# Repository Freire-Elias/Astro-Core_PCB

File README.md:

# Astro-Core PCB

Placa de controle baseada em **ESP32**, projetada para a equipe de robótica competitiva OBR **AstroTech**.

---

## What is this project?

This project was designed to create a central module for sensors, control, motors, and monitoring of an OBR robot.
This repository contains all the hardware files (PCB and schematics) for this board.

---

## 3D Board Render

---

## Board Schematic

---

## License

This project is under license **MIT**.  
See [LICENSE](LICENSE) for more details.

---

## 👤 Author

Created by **Elias Freire**  
GitHub: https://github.com/Freire-Elias

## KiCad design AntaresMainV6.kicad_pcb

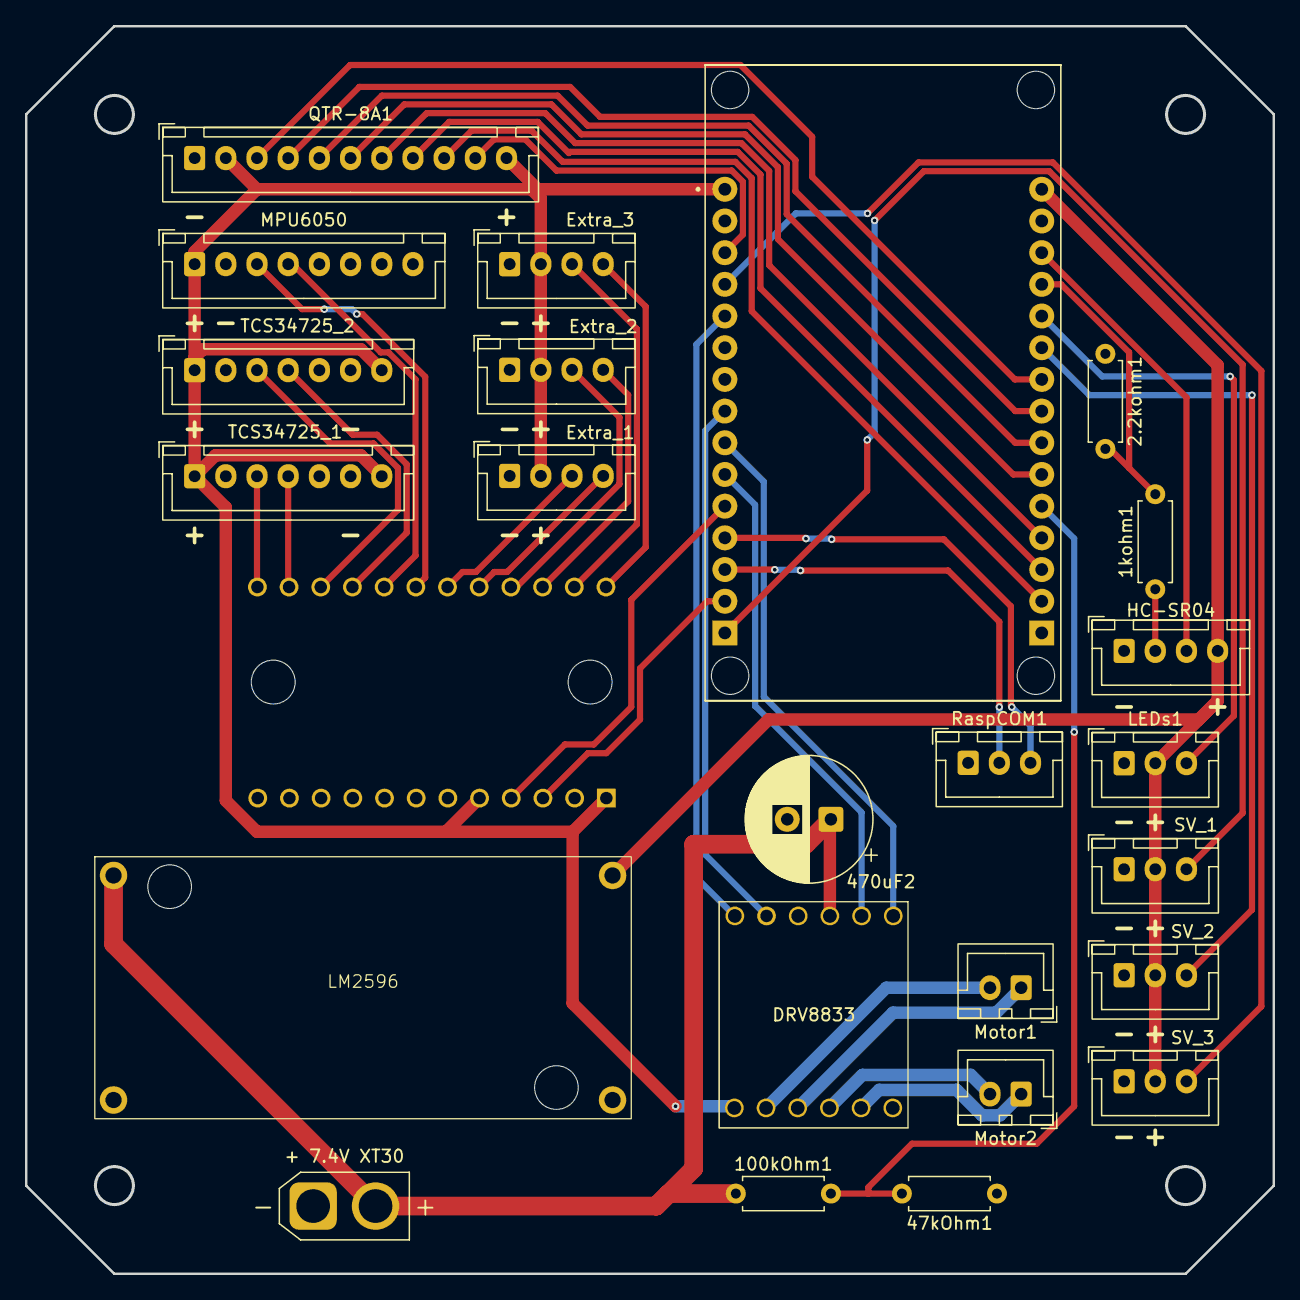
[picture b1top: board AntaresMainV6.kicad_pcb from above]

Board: 2 copper layers, 100.0 x 100.0 mm, 25 parts (1 on the bottom side), 44 nets.

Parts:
1kohm1, 2.2kohm1, 47kOhm1, 100kOhm1: R; R_Axial_DIN0207_L6.3mm_D2.5mm_P7.62mm_Horizontal
470uF2: C_Polarized; CP_Radial_D10.0mm_P3.50mm
+ 7.4V XT30: Conn_01x02_Socket; AMASS_XT30U-M_1x02_P5.0mm_Vertical
DRV8833: DRV8833
Extra_1, Extra_2, Extra_3: Conn_01x04_Socket; JST_XH_B4B-XH-A_1x04_P2.50mm_Vertical
HC-SR04: Conn_01x04_Socket; JST_XH_B4B-XH-A_1x04_P2.50mm_Vertical
LEDs1: Conn_01x03_Socket; JST_XH_B3B-XH-A_1x03_P2.50mm_Vertical
LM2596: Lm2596 DC-DC Buck; Lm2596_ALT
MPU6050: Conn_01x08_Socket; JST_XH_B8B-XH-A_1x08_P2.50mm_Vertical
Motor1, Motor2: Conn_01x02_Socket; JST_XH_B2B-XH-A_1x02_P2.50mm_Vertical
QTR-8A1: Conn_01x11_Socket; JST_XH_B11B-XH-A_1x11_P2.50mm_Vertical
RaspCOM1: Conn_01x03_Socket; JST_XH_B3B-XH-A_1x03_P2.50mm_Vertical
SV_1, SV_2, SV_3: Conn_01x03_Socket; JST_XH_B3B-XH-A_1x03_P2.50mm_Vertical
TCA1: 2717; TCA9548_ALT
TCS34725_1, TCS34725_2: Conn_01x07_Socket; JST_XH_B7B-XH-A_1x07_P2.50mm_Vertical
U3: ESP32-DEVKIT-V1; MODULE_ESP32_DEVKIT_V1

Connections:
/0+: 100kOhm1.1, 470uF2.1, + 7.4V XT30.2, DRV8833.4 (VCC), LM2596.in+ (IN+)
/3.3v: DRV8833.7 (EEP), Extra_1.2, Extra_2.2, Extra_3.2, MPU6050.1, QTR-8A1.2, QTR-8A1.11, TCA1.RST, TCA1.VIN, TCS34725_1.1, TCS34725_1.7, TCS34725_2.1, TCS34725_2.7, U3.3V3
/5V_LM: HC-SR04.4, LEDs1.2, LM2596.out+ (OUT+), SV_1.2, SV_2.2, SV_3.2, U3.VIN
/BAT: 47kOhm1.2, 100kOhm1.2, U3.35 (D35)
/Echo3.3v: 1kohm1.2, 2.2kohm1.2, U3.12 (D12)
/Echo5v: 1kohm1.1, HC-SR04.2
/IN1: DRV8833.1 (IN1), U3.4 (D4)
/IN2: DRV8833.2 (IN2), U3.5 (D5)
/IN3: DRV8833.5 (IN3), U3.19 (D19)
/IN4: DRV8833.6 (IN4), U3.18 (D18)
/LED: LEDs1.3, U3.14 (D14)
/Motors/OUT1: DRV8833.8 (OUT1), Motor1.2
/Motors/OUT2: DRV8833.9 (OUT2), Motor1.1
/Motors/OUT3: DRV8833.10 (OUT3), Motor2.2
/Motors/OUT4: DRV8833.11 (OUT4), Motor2.1
/Multiplexers/SCL_5: Extra_1.4, TCA1.SC5 (SCL5)
/Multiplexers/SCL_6: Extra_2.4, TCA1.SC6 (SCL6)
/Multiplexers/SCL_7: Extra_3.4, TCA1.SC7 (SCL7)
/Multiplexers/SCL_IMU: MPU6050.3, TCA1.SC4 (SCL4)
/Multiplexers/SCL_S1: TCA1.SC2 (SCL2), TCS34725_1.4
/Multiplexers/SCL_S2: TCA1.SC3, TCS34725_2.4
/Multiplexers/SDA_5: Extra_1.3, TCA1.SD5 (SDA5)
/Multiplexers/SDA_6: Extra_2.3, TCA1.SD6 (SDA6)
/Multiplexers/SDA_7: Extra_3.3, TCA1.SD7 (SDA7)
/Multiplexers/SDA_IMU: MPU6050.4, TCA1.SD4 (SDA4)
/Multiplexers/SDA_S1: TCA1.SD2 (SDA2), TCS34725_1.3
/Multiplexers/SDA_S2: TCA1.SD3 (SDA3), TCS34725_2.3
/OUT1: QTR-8A1.3, U3.26 (D26)
/OUT2: QTR-8A1.4, U3.25 (D25)
/OUT3: QTR-8A1.5, U3.33 (D33)
/OUT4: QTR-8A1.6, U3.32 (D32)
/OUT5: QTR-8A1.7, U3.34 (D34)
/OUT6: QTR-8A1.8, U3.VN
/OUT7: QTR-8A1.9, U3.VP
/OUT8: QTR-8A1.10, U3.15 (D15)
/RX: RaspCOM1.3, U3.RX0
/SCL: TCA1.SCL, U3.21 (D21)
/SDA: TCA1.SDA, U3.22 (D22)
/SV_1: SV_1.3, U3.23 (D23)
/SV_2: SV_2.3, U3.27 (D27)
/SV_3: SV_3.3, U3.2 (D2)
/TX: RaspCOM1.2, U3.TX0
/Trig: HC-SR04.3, U3.13 (D13)
GND: 2.2kohm1.1, 47kOhm1.1, 470uF2.2, + 7.4V XT30.1, DRV8833.3 (GND), Extra_1.1, Extra_2.1, Extra_3.1, HC-SR04.1, LEDs1.1, LM2596.in- (IN-), LM2596.out- (OUT-), MPU6050.2, QTR-8A1.1, RaspCOM1.1, SV_1.1, SV_2.1, SV_3.1, TCA1.A0, TCA1.A1, TCA1.A2, TCA1.GND, TCS34725_1.6, TCS34725_2.6, U3.GND

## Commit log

2026-02-03 commit inicial
2026-02-05 Mudanças nos footprints
2026-02-08 placa semi pronta
2026-02-09 Modificações semi finais
2026-02-09 Faltando apenas LED e verificação
2026-02-10 Decisão final da multiplexadora
2026-02-10 Remoção da mux
2026-02-12 erros ajustados e placa reformulada
2026-02-14 Placa Finalizada
2026-02-14 Rename AntaresMainV6.kicad_pcb to hardware/AntaresMainV6.kicad_pcb
2026-02-14 Rename AntaresMainV6.kicad_pro to hardware/AntaresMainV6.kicad_pro
2026-02-14 Rename Alimentação.kicad_sch to circuit/Alimentação.kicad_sch
2026-02-14 Rename AntaresMainV6.kicad_sch to circuit/AntaresMainV6.kicad_sch
2026-02-14 Rename Motors.kicad_sch to circuit/Motors.kicad_sch
2026-02-14 Rename Multiplexers.kicad_sch to circuit/Multiplexers.kicad_sch
2026-02-14 Rename hardware/docs/images/img.md to docs/images/img.md
2026-02-14 Rename circuit/Alimentação.kicad_sch to docs/schematic/Alimentação.kicad_sch
2026-02-14 Rename circuit/AntaresMainV6.kicad_sch to docs/schematic/AntaresMainV6.kicad_sch
2026-02-14 Rename circuit/Motors.kicad_sch to docs/schematic/Motors.kicad_sch
2026-02-14 Rename circuit/Multiplexers.kicad_sch to docs/schematic/Multiplexers.kicad_sch
2026-02-14 Create teste
2026-02-14 Create LICENSE
